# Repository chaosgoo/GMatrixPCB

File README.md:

# GMatrixPCB

该Repo为GMatrix的PCB文件，绘制软件为Autodesk Eagle。
目录下GMatrix.zip为打包的Gerber文件，直接提交到工厂即可。

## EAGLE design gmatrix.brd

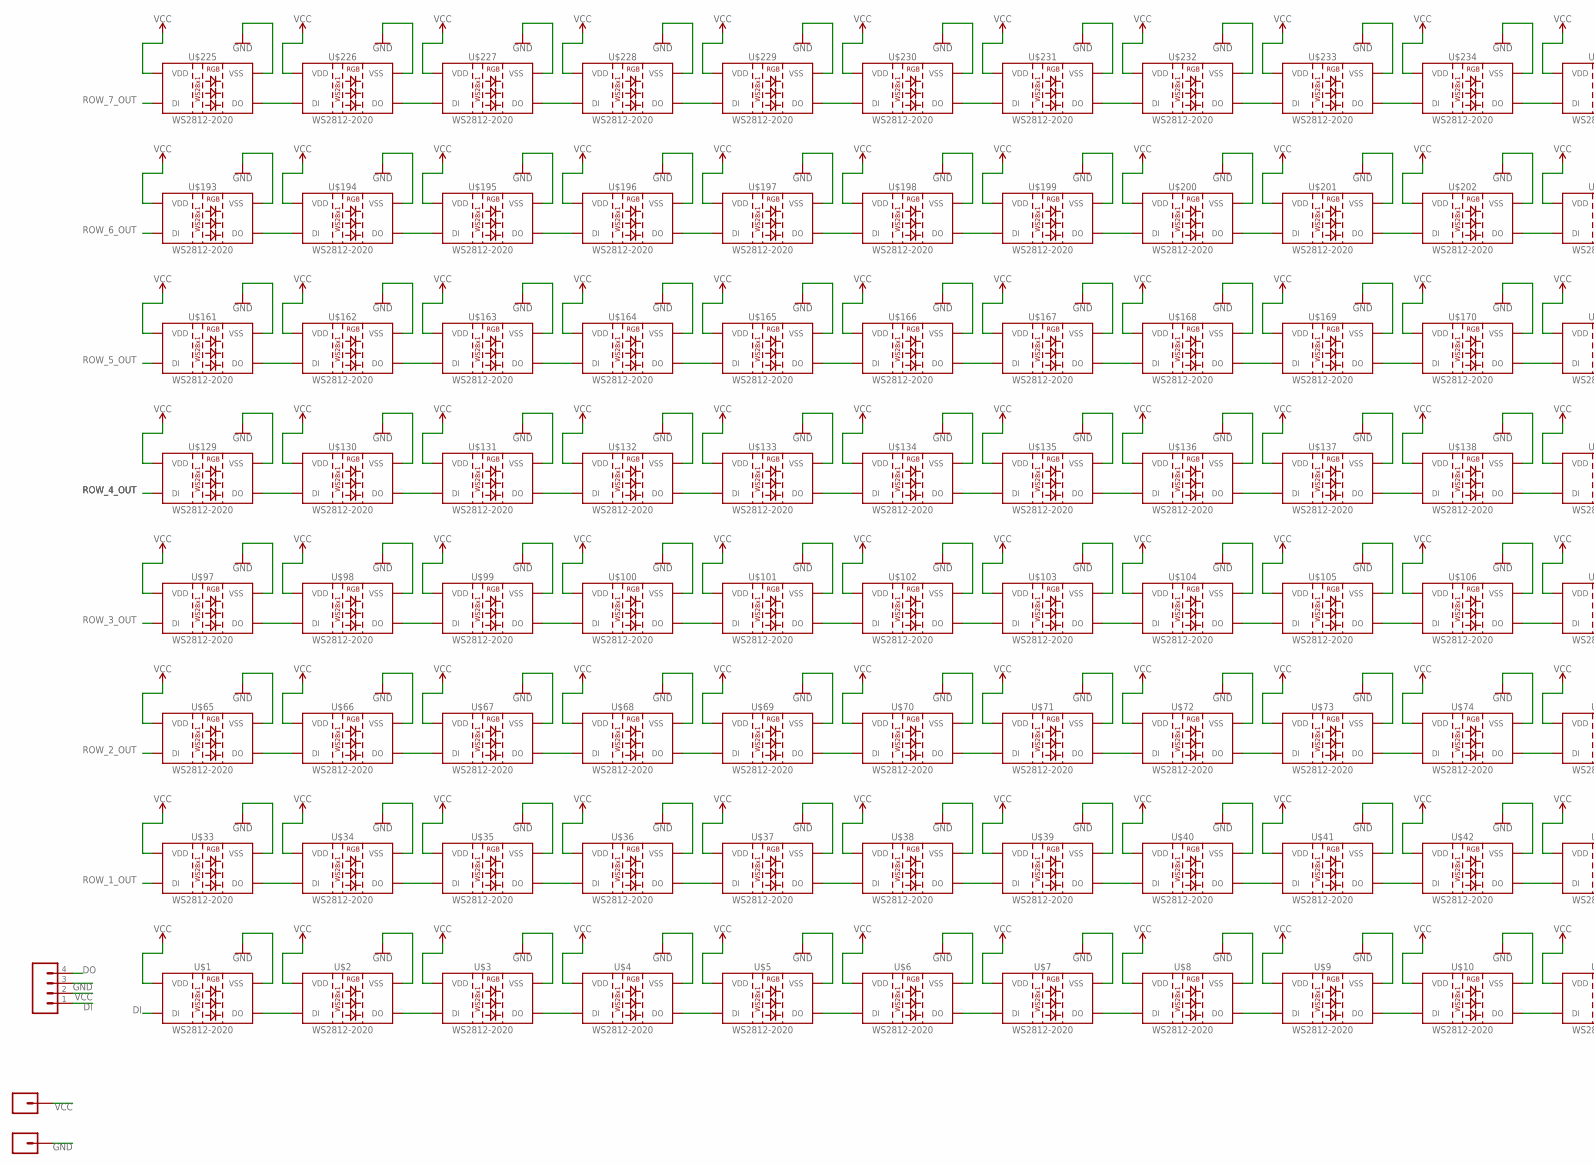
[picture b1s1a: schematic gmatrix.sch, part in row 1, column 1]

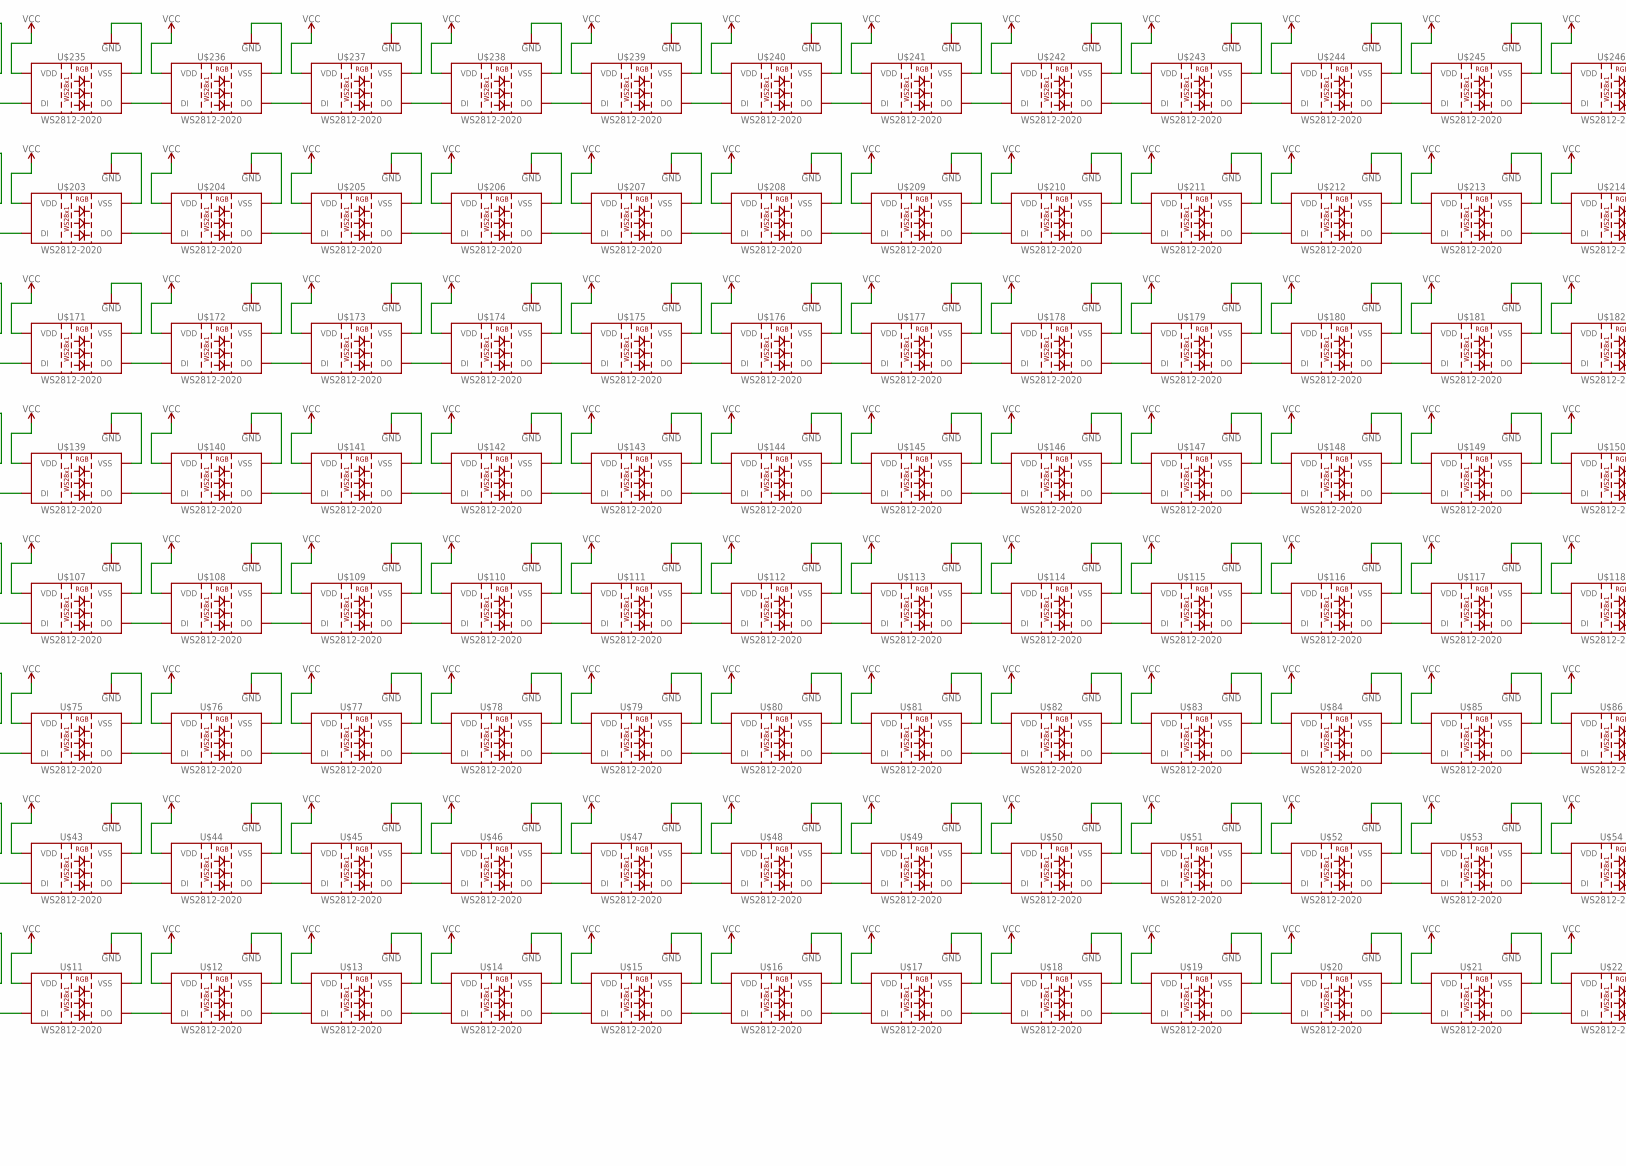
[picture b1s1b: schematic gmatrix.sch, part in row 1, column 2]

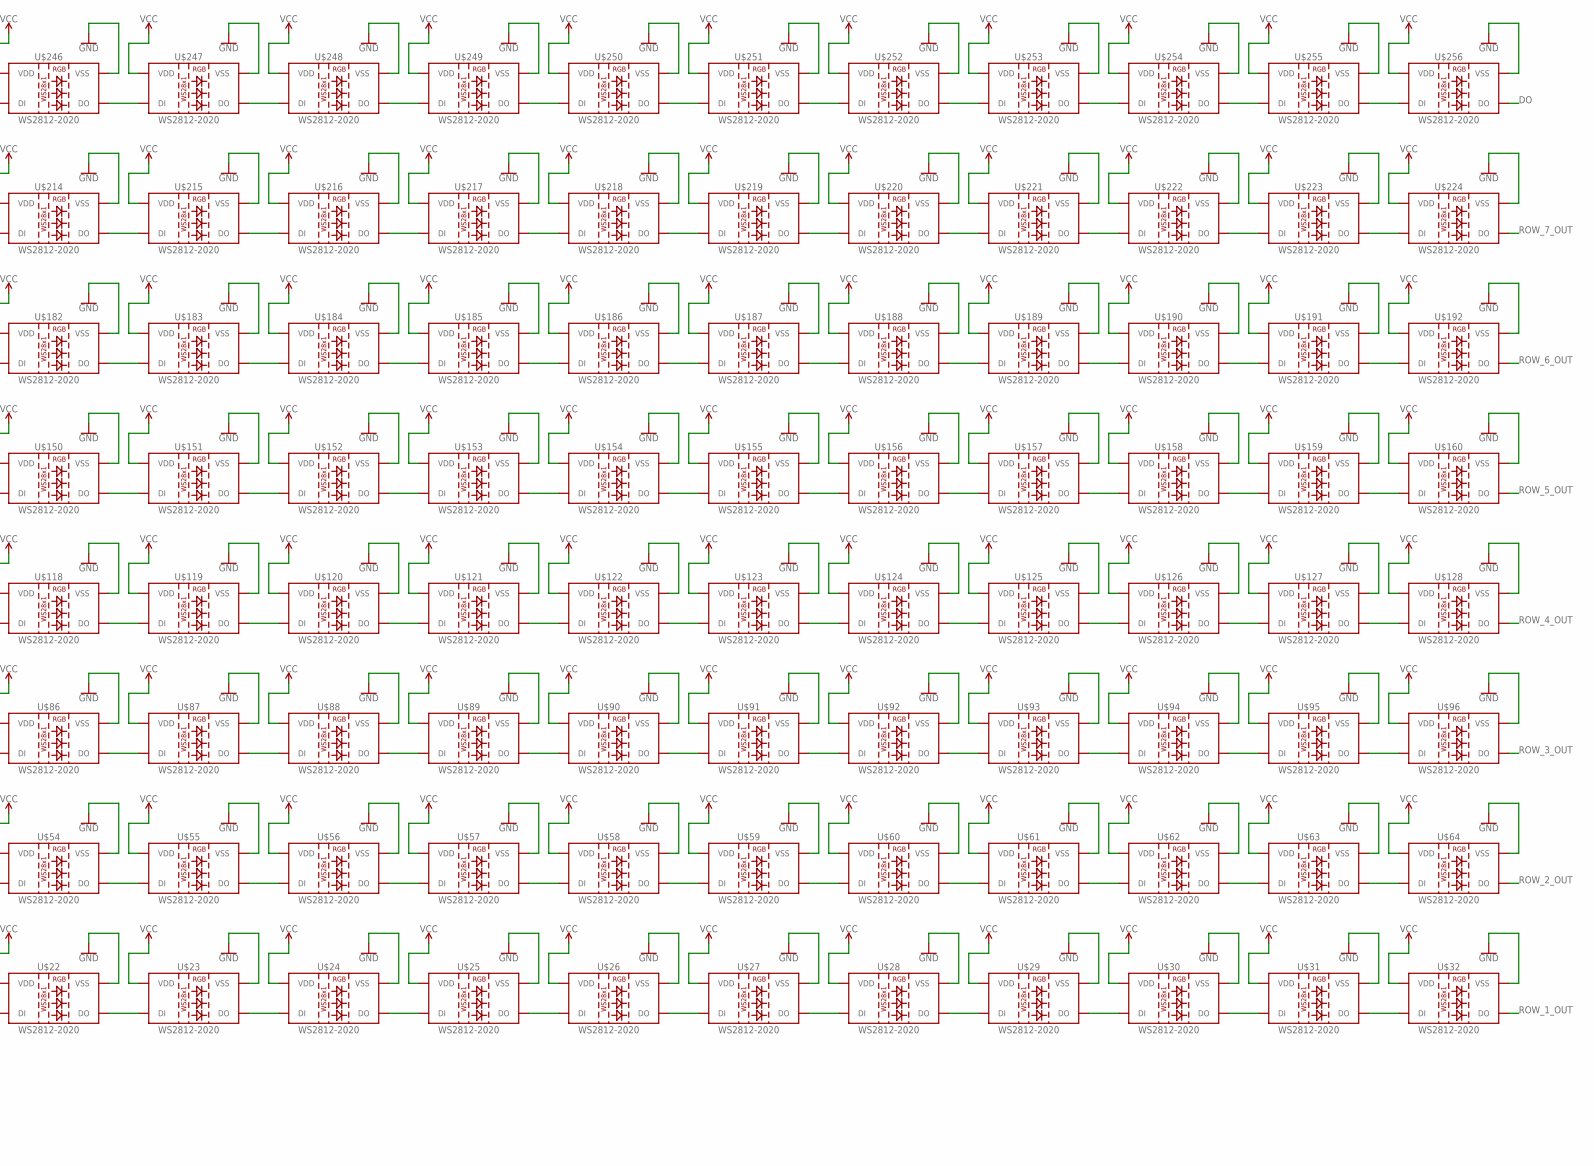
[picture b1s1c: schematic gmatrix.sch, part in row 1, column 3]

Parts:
J1: CONN_041X04_NO_SILK; 1X04_NO_SILK
J2, J3: CONN_01PTH_NO_SILK_KIT; 1X01NS_KIT
U$1, U$2, U$3, U$4, U$5, U$6, U$7, U$8, U$9, U$10, U$11, U$12, U$13, U$14, U$15, U$16, U$17, U$18, U$19, U$20, U$21, U$22, U$23, U$24, U$25, U$26, U$27, U$28, U$29, U$30, U$31, U$32, U$33, U$34, U$35, U$36, U$37, U$38, U$39, U$40, U$41, U$42, U$43, U$44, U$45, U$46, U$47, U$48, U$49, U$50, U$51, U$52, U$53, U$54, U$55, U$56, U$57, U$58, U$59, U$60, U$61, U$62, U$63, U$64, U$65, U$66, U$67, U$68, U$69, U$70, U$71, U$72, U$73, U$74, U$75, U$76, U$77, U$78, U$79, U$80, U$81, U$82, U$83, U$84, U$85, U$86, U$87, U$88, U$89, U$90, U$91, U$92, U$93, U$94, U$95, U$96, U$97, U$98, U$99, U$100, U$101, U$102, U$103, U$104, U$105, U$106, U$107, U$108, U$109, U$110, U$111, U$112, U$113, U$114, U$115, U$116, U$117, U$118, U$119, U$120, U$121, U$122, U$123, U$124, U$125, U$126, U$127, U$128, U$129, U$130, U$131, U$132, U$133, U$134, U$135, U$136, U$137, U$138, U$139, U$140, U$141, U$142, U$143, U$144, U$145, U$146, U$147, U$148, U$149, U$150, U$151, U$152, U$153, U$154, U$155, U$156, U$157, U$158, U$159, U$160, U$161, U$162, U$163, U$164, U$165, U$166, U$167, U$168, U$169, U$170, U$171, U$172, U$173, U$174, U$175, U$176, U$177, U$178, U$179, U$180, U$181, U$182, U$183, U$184, U$185, U$186, U$187, U$188, U$189, U$190, U$191, U$192, U$193, U$194, U$195, U$196, U$197, U$198, U$199, U$200, U$201, U$202, U$203, U$204, U$205, U$206, U$207, U$208, U$209, U$210, U$211, U$212, U$213, U$214, U$215, U$216, U$217, U$218, U$219, U$220, U$221, U$222, U$223, U$224, U$225, U$226, U$227, U$228, U$229, U$230, U$231, U$232, U$233, U$234, U$235, U$236, U$237, U$238, U$239, U$240, U$241, U$242, U$243, U$244, U$245, U$246, U$247, U$248, U$249, U$250, U$251, U$252, U$253, U$254, U$255, U$256: WS2812-2020

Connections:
DI: J1.1, U$1.3 (DI)
DO: J1.4, U$256.1 (DO)
GND: J1.3, J3.1, U$1.2 (VSS), U$2.2 (VSS), U$3.2 (VSS), U$4.2 (VSS), U$5.2 (VSS), U$6.2 (VSS), U$7.2 (VSS), U$8.2 (VSS), U$9.2 (VSS), U$10.2 (VSS), U$11.2 (VSS), U$12.2 (VSS), U$13.2 (VSS), U$14.2 (VSS), U$15.2 (VSS), U$16.2 (VSS), U$17.2 (VSS), U$18.2 (VSS), U$19.2 (VSS), U$20.2 (VSS), U$21.2 (VSS), U$22.2 (VSS), U$23.2 (VSS), U$24.2 (VSS), U$25.2 (VSS), U$26.2 (VSS), U$27.2 (VSS), U$28.2 (VSS), U$29.2 (VSS), U$30.2 (VSS), U$31.2 (VSS), U$32.2 (VSS), U$33.2 (VSS), U$34.2 (VSS), U$35.2 (VSS), U$36.2 (VSS), U$37.2 (VSS), U$38.2 (VSS), U$39.2 (VSS), U$40.2 (VSS), U$41.2 (VSS), U$42.2 (VSS), U$43.2 (VSS), U$44.2 (VSS), U$45.2 (VSS), U$46.2 (VSS), U$47.2 (VSS), U$48.2 (VSS), U$49.2 (VSS), U$50.2 (VSS), U$51.2 (VSS), U$52.2 (VSS), U$53.2 (VSS), U$54.2 (VSS), U$55.2 (VSS), U$56.2 (VSS), U$57.2 (VSS), U$58.2 (VSS), U$59.2 (VSS), U$60.2 (VSS), U$61.2 (VSS), U$62.2 (VSS), U$63.2 (VSS), U$64.2 (VSS), U$65.2 (VSS), U$66.2 (VSS), U$67.2 (VSS), U$68.2 (VSS), U$69.2 (VSS), U$70.2 (VSS), U$71.2 (VSS), U$72.2 (VSS), U$73.2 (VSS), U$74.2 (VSS), U$75.2 (VSS), U$76.2 (VSS), U$77.2 (VSS), U$78.2 (VSS), U$79.2 (VSS), U$80.2 (VSS), U$81.2 (VSS), U$82.2 (VSS), U$83.2 (VSS), U$84.2 (VSS), U$85.2 (VSS), U$86.2 (VSS), U$87.2 (VSS), U$88.2 (VSS), U$89.2 (VSS), U$90.2 (VSS), U$91.2 (VSS), U$92.2 (VSS), U$93.2 (VSS), U$94.2 (VSS), U$95.2 (VSS), U$96.2 (VSS), U$97.2 (VSS), U$98.2 (VSS), U$99.2 (VSS), U$100.2 (VSS), U$101.2 (VSS), U$102.2 (VSS), U$103.2 (VSS), U$104.2 (VSS), U$105.2 (VSS), U$106.2 (VSS), U$107.2 (VSS), U$108.2 (VSS), U$109.2 (VSS), U$110.2 (VSS), U$111.2 (VSS), U$112.2 (VSS), U$113.2 (VSS), U$114.2 (VSS), U$115.2 (VSS), U$116.2 (VSS), U$117.2 (VSS), U$118.2 (VSS), U$119.2 (VSS), U$120.2 (VSS), U$121.2 (VSS), U$122.2 (VSS), U$123.2 (VSS), U$124.2 (VSS), U$125.2 (VSS), U$126.2 (VSS), U$127.2 (VSS), U$128.2 (VSS), U$129.2 (VSS), U$130.2 (VSS), U$131.2 (VSS), U$132.2 (VSS), U$133.2 (VSS), U$134.2 (VSS), U$135.2 (VSS), U$136.2 (VSS), U$137.2 (VSS), U$138.2 (VSS), U$139.2 (VSS), U$140.2 (VSS), U$141.2 (VSS), U$142.2 (VSS), U$143.2 (VSS), U$144.2 (VSS), U$145.2 (VSS), U$146.2 (VSS), U$147.2 (VSS), U$148.2 (VSS), U$149.2 (VSS), U$150.2 (VSS), U$151.2 (VSS), U$152.2 (VSS), U$153.2 (VSS), U$154.2 (VSS), U$155.2 (VSS), U$156.2 (VSS), U$157.2 (VSS), U$158.2 (VSS), U$159.2 (VSS), U$160.2 (VSS), U$161.2 (VSS), U$162.2 (VSS), U$163.2 (VSS), U$164.2 (VSS), U$165.2 (VSS), U$166.2 (VSS), U$167.2 (VSS), U$168.2 (VSS), U$169.2 (VSS), U$170.2 (VSS), U$171.2 (VSS), U$172.2 (VSS), U$173.2 (VSS), U$174.2 (VSS), U$175.2 (VSS), U$176.2 (VSS), U$177.2 (VSS), U$178.2 (VSS), U$179.2 (VSS), U$180.2 (VSS), U$181.2 (VSS), U$182.2 (VSS), U$183.2 (VSS), U$184.2 (VSS), U$185.2 (VSS), U$186.2 (VSS), U$187.2 (VSS), U$188.2 (VSS), U$189.2 (VSS), U$190.2 (VSS), U$191.2 (VSS), U$192.2 (VSS), U$193.2 (VSS), U$194.2 (VSS), U$195.2 (VSS), U$196.2 (VSS), U$197.2 (VSS), U$198.2 (VSS), U$199.2 (VSS), U$200.2 (VSS), U$201.2 (VSS), U$202.2 (VSS), U$203.2 (VSS), U$204.2 (VSS), U$205.2 (VSS), U$206.2 (VSS), U$207.2 (VSS), U$208.2 (VSS), U$209.2 (VSS), U$210.2 (VSS), U$211.2 (VSS), U$212.2 (VSS), U$213.2 (VSS), U$214.2 (VSS), U$215.2 (VSS), U$216.2 (VSS), U$217.2 (VSS), U$218.2 (VSS), U$219.2 (VSS), U$220.2 (VSS), U$221.2 (VSS), U$222.2 (VSS), U$223.2 (VSS), U$224.2 (VSS), U$225.2 (VSS), U$226.2 (VSS), U$227.2 (VSS), U$228.2 (VSS), U$229.2 (VSS), U$230.2 (VSS), U$231.2 (VSS), U$232.2 (VSS), U$233.2 (VSS), U$234.2 (VSS), U$235.2 (VSS), U$236.2 (VSS), U$237.2 (VSS), U$238.2 (VSS), U$239.2 (VSS), U$240.2 (VSS), U$241.2 (VSS), U$242.2 (VSS), U$243.2 (VSS), U$244.2 (VSS), U$245.2 (VSS), U$246.2 (VSS), U$247.2 (VSS), U$248.2 (VSS), U$249.2 (VSS), U$250.2 (VSS), U$251.2 (VSS), U$252.2 (VSS), U$253.2 (VSS), U$254.2 (VSS), U$255.2 (VSS), U$256.2 (VSS)
unnamed: U$1.1 (DO), U$2.3 (DI)
unnamed: U$2.1 (DO), U$3.3 (DI)
unnamed: U$3.1 (DO), U$4.3 (DI)
unnamed: U$4.1 (DO), U$5.3 (DI)
unnamed: U$5.1 (DO), U$6.3 (DI)
unnamed: U$6.1 (DO), U$7.3 (DI)
unnamed: U$7.1 (DO), U$8.3 (DI)
unnamed: U$8.1 (DO), U$9.3 (DI)
unnamed: U$9.1 (DO), U$10.3 (DI)
unnamed: U$10.1 (DO), U$11.3 (DI)
unnamed: U$11.1 (DO), U$12.3 (DI)
unnamed: U$12.1 (DO), U$13.3 (DI)
unnamed: U$13.1 (DO), U$14.3 (DI)
unnamed: U$14.1 (DO), U$15.3 (DI)
unnamed: U$15.1 (DO), U$16.3 (DI)
unnamed: U$16.1 (DO), U$17.3 (DI)
unnamed: U$17.1 (DO), U$18.3 (DI)
unnamed: U$18.1 (DO), U$19.3 (DI)
unnamed: U$19.1 (DO), U$20.3 (DI)
unnamed: U$20.1 (DO), U$21.3 (DI)
unnamed: U$21.1 (DO), U$22.3 (DI)
unnamed: U$22.1 (DO), U$23.3 (DI)
unnamed: U$23.1 (DO), U$24.3 (DI)
unnamed: U$24.1 (DO), U$25.3 (DI)
unnamed: U$25.1 (DO), U$26.3 (DI)
unnamed: U$26.1 (DO), U$27.3 (DI)
unnamed: U$27.1 (DO), U$28.3 (DI)
unnamed: U$28.1 (DO), U$29.3 (DI)
unnamed: U$29.1 (DO), U$30.3 (DI)
unnamed: U$30.1 (DO), U$31.3 (DI)
unnamed: U$31.1 (DO), U$32.3 (DI)
unnamed: U$33.1 (DO), U$34.3 (DI)
unnamed: U$34.1 (DO), U$35.3 (DI)
unnamed: U$35.1 (DO), U$36.3 (DI)
unnamed: U$36.1 (DO), U$37.3 (DI)
unnamed: U$37.1 (DO), U$38.3 (DI)
unnamed: U$38.1 (DO), U$39.3 (DI)
unnamed: U$39.1 (DO), U$40.3 (DI)
unnamed: U$40.1 (DO), U$41.3 (DI)
unnamed: U$41.1 (DO), U$42.3 (DI)
unnamed: U$42.1 (DO), U$43.3 (DI)
unnamed: U$43.1 (DO), U$44.3 (DI)
unnamed: U$44.1 (DO), U$45.3 (DI)
unnamed: U$45.1 (DO), U$46.3 (DI)
unnamed: U$46.1 (DO), U$47.3 (DI)
unnamed: U$47.1 (DO), U$48.3 (DI)
unnamed: U$48.1 (DO), U$49.3 (DI)
unnamed: U$49.1 (DO), U$50.3 (DI)
unnamed: U$50.1 (DO), U$51.3 (DI)
unnamed: U$51.1 (DO), U$52.3 (DI)
unnamed: U$52.1 (DO), U$53.3 (DI)
unnamed: U$53.1 (DO), U$54.3 (DI)
unnamed: U$54.1 (DO), U$55.3 (DI)
unnamed: U$55.1 (DO), U$56.3 (DI)
unnamed: U$56.1 (DO), U$57.3 (DI)
unnamed: U$57.1 (DO), U$58.3 (DI)
unnamed: U$58.1 (DO), U$59.3 (DI)
unnamed: U$59.1 (DO), U$60.3 (DI)
unnamed: U$60.1 (DO), U$61.3 (DI)
unnamed: U$61.1 (DO), U$62.3 (DI)
unnamed: U$62.1 (DO), U$63.3 (DI)
unnamed: U$63.1 (DO), U$64.3 (DI)
unnamed: U$65.1 (DO), U$66.3 (DI)
unnamed: U$66.1 (DO), U$67.3 (DI)
unnamed: U$67.1 (DO), U$68.3 (DI)
unnamed: U$68.1 (DO), U$69.3 (DI)
unnamed: U$69.1 (DO), U$70.3 (DI)
unnamed: U$70.1 (DO), U$71.3 (DI)
unnamed: U$71.1 (DO), U$72.3 (DI)
unnamed: U$72.1 (DO), U$73.3 (DI)
unnamed: U$73.1 (DO), U$74.3 (DI)
unnamed: U$74.1 (DO), U$75.3 (DI)
unnamed: U$75.1 (DO), U$76.3 (DI)
unnamed: U$76.1 (DO), U$77.3 (DI)
unnamed: U$77.1 (DO), U$78.3 (DI)
unnamed: U$78.1 (DO), U$79.3 (DI)
unnamed: U$79.1 (DO), U$80.3 (DI)
unnamed: U$80.1 (DO), U$81.3 (DI)
unnamed: U$81.1 (DO), U$82.3 (DI)
unnamed: U$82.1 (DO), U$83.3 (DI)
unnamed: U$83.1 (DO), U$84.3 (DI)
unnamed: U$84.1 (DO), U$85.3 (DI)
unnamed: U$85.1 (DO), U$86.3 (DI)
unnamed: U$86.1 (DO), U$87.3 (DI)
unnamed: U$87.1 (DO), U$88.3 (DI)
unnamed: U$88.1 (DO), U$89.3 (DI)
unnamed: U$89.1 (DO), U$90.3 (DI)
unnamed: U$90.1 (DO), U$91.3 (DI)
unnamed: U$91.1 (DO), U$92.3 (DI)
unnamed: U$92.1 (DO), U$93.3 (DI)
unnamed: U$93.1 (DO), U$94.3 (DI)
unnamed: U$94.1 (DO), U$95.3 (DI)
unnamed: U$95.1 (DO), U$96.3 (DI)
unnamed: U$97.1 (DO), U$98.3 (DI)
unnamed: U$98.1 (DO), U$99.3 (DI)
unnamed: U$99.1 (DO), U$100.3 (DI)
unnamed: U$100.1 (DO), U$101.3 (DI)
unnamed: U$101.1 (DO), U$102.3 (DI)
unnamed: U$102.1 (DO), U$103.3 (DI)
unnamed: U$103.1 (DO), U$104.3 (DI)
unnamed: U$104.1 (DO), U$105.3 (DI)
unnamed: U$105.1 (DO), U$106.3 (DI)
unnamed: U$106.1 (DO), U$107.3 (DI)
unnamed: U$107.1 (DO), U$108.3 (DI)
unnamed: U$108.1 (DO), U$109.3 (DI)
unnamed: U$109.1 (DO), U$110.3 (DI)
unnamed: U$110.1 (DO), U$111.3 (DI)
unnamed: U$111.1 (DO), U$112.3 (DI)
unnamed: U$112.1 (DO), U$113.3 (DI)
unnamed: U$113.1 (DO), U$114.3 (DI)
unnamed: U$114.1 (DO), U$115.3 (DI)
unnamed: U$115.1 (DO), U$116.3 (DI)
unnamed: U$116.1 (DO), U$117.3 (DI)
unnamed: U$117.1 (DO), U$118.3 (DI)
unnamed: U$118.1 (DO), U$119.3 (DI)
unnamed: U$119.1 (DO), U$120.3 (DI)
unnamed: U$120.1 (DO), U$121.3 (DI)
unnamed: U$121.1 (DO), U$122.3 (DI)
unnamed: U$122.1 (DO), U$123.3 (DI)
unnamed: U$123.1 (DO), U$124.3 (DI)
unnamed: U$124.1 (DO), U$125.3 (DI)
unnamed: U$125.1 (DO), U$126.3 (DI)
unnamed: U$126.1 (DO), U$127.3 (DI)
unnamed: U$127.1 (DO), U$128.3 (DI)
unnamed: U$129.1 (DO), U$130.3 (DI)
unnamed: U$130.1 (DO), U$131.3 (DI)
unnamed: U$131.1 (DO), U$132.3 (DI)
unnamed: U$132.1 (DO), U$133.3 (DI)
unnamed: U$133.1 (DO), U$134.3 (DI)
unnamed: U$134.1 (DO), U$135.3 (DI)
unnamed: U$135.1 (DO), U$136.3 (DI)
unnamed: U$136.1 (DO), U$137.3 (DI)
unnamed: U$137.1 (DO), U$138.3 (DI)
unnamed: U$138.1 (DO), U$139.3 (DI)
unnamed: U$139.1 (DO), U$140.3 (DI)
unnamed: U$140.1 (DO), U$141.3 (DI)
unnamed: U$141.1 (DO), U$142.3 (DI)
unnamed: U$142.1 (DO), U$143.3 (DI)
unnamed: U$143.1 (DO), U$144.3 (DI)
unnamed: U$144.1 (DO), U$145.3 (DI)
unnamed: U$145.1 (DO), U$146.3 (DI)
unnamed: U$146.1 (DO), U$147.3 (DI)
unnamed: U$147.1 (DO), U$148.3 (DI)
unnamed: U$148.1 (DO), U$149.3 (DI)
unnamed: U$149.1 (DO), U$150.3 (DI)
unnamed: U$150.1 (DO), U$151.3 (DI)
unnamed: U$151.1 (DO), U$152.3 (DI)
unnamed: U$152.1 (DO), U$153.3 (DI)
unnamed: U$153.1 (DO), U$154.3 (DI)
unnamed: U$154.1 (DO), U$155.3 (DI)
unnamed: U$155.1 (DO), U$156.3 (DI)
unnamed: U$156.1 (DO), U$157.3 (DI)
unnamed: U$157.1 (DO), U$158.3 (DI)
unnamed: U$158.1 (DO), U$159.3 (DI)
unnamed: U$159.1 (DO), U$160.3 (DI)
unnamed: U$161.1 (DO), U$162.3 (DI)
unnamed: U$162.1 (DO), U$163.3 (DI)
unnamed: U$163.1 (DO), U$164.3 (DI)
unnamed: U$164.1 (DO), U$165.3 (DI)
unnamed: U$165.1 (DO), U$166.3 (DI)
unnamed: U$166.1 (DO), U$167.3 (DI)
unnamed: U$167.1 (DO), U$168.3 (DI)
unnamed: U$168.1 (DO), U$169.3 (DI)
unnamed: U$169.1 (DO), U$170.3 (DI)
unnamed: U$170.1 (DO), U$171.3 (DI)
unnamed: U$171.1 (DO), U$172.3 (DI)
unnamed: U$172.1 (DO), U$173.3 (DI)
unnamed: U$173.1 (DO), U$174.3 (DI)
unnamed: U$174.1 (DO), U$175.3 (DI)
unnamed: U$175.1 (DO), U$176.3 (DI)
unnamed: U$176.1 (DO), U$177.3 (DI)
unnamed: U$177.1 (DO), U$178.3 (DI)
unnamed: U$178.1 (DO), U$179.3 (DI)
unnamed: U$179.1 (DO), U$180.3 (DI)
unnamed: U$180.1 (DO), U$181.3 (DI)
unnamed: U$181.1 (DO), U$182.3 (DI)
unnamed: U$182.1 (DO), U$183.3 (DI)
unnamed: U$183.1 (DO), U$184.3 (DI)
unnamed: U$184.1 (DO), U$185.3 (DI)
unnamed: U$185.1 (DO), U$186.3 (DI)
unnamed: U$186.1 (DO), U$187.3 (DI)
unnamed: U$187.1 (DO), U$188.3 (DI)
unnamed: U$188.1 (DO), U$189.3 (DI)
unnamed: U$189.1 (DO), U$190.3 (DI)
unnamed: U$190.1 (DO), U$191.3 (DI)
unnamed: U$191.1 (DO), U$192.3 (DI)
unnamed: U$193.1 (DO), U$194.3 (DI)
unnamed: U$194.1 (DO), U$195.3 (DI)
unnamed: U$195.1 (DO), U$196.3 (DI)
unnamed: U$196.1 (DO), U$197.3 (DI)
unnamed: U$197.1 (DO), U$198.3 (DI)
unnamed: U$198.1 (DO), U$199.3 (DI)
unnamed: U$199.1 (DO), U$200.3 (DI)
unnamed: U$200.1 (DO), U$201.3 (DI)
unnamed: U$201.1 (DO), U$202.3 (DI)
unnamed: U$202.1 (DO), U$203.3 (DI)
unnamed: U$203.1 (DO), U$204.3 (DI)
unnamed: U$204.1 (DO), U$205.3 (DI)
unnamed: U$205.1 (DO), U$206.3 (DI)
unnamed: U$206.1 (DO), U$207.3 (DI)
unnamed: U$207.1 (DO), U$208.3 (DI)
unnamed: U$208.1 (DO), U$209.3 (DI)
unnamed: U$209.1 (DO), U$210.3 (DI)
unnamed: U$210.1 (DO), U$211.3 (DI)
unnamed: U$211.1 (DO), U$212.3 (DI)
unnamed: U$212.1 (DO), U$213.3 (DI)
unnamed: U$213.1 (DO), U$214.3 (DI)
unnamed: U$214.1 (DO), U$215.3 (DI)
unnamed: U$215.1 (DO), U$216.3 (DI)
unnamed: U$216.1 (DO), U$217.3 (DI)
unnamed: U$217.1 (DO), U$218.3 (DI)
unnamed: U$218.1 (DO), U$219.3 (DI)
unnamed: U$219.1 (DO), U$220.3 (DI)
unnamed: U$220.1 (DO), U$221.3 (DI)
unnamed: U$221.1 (DO), U$222.3 (DI)
unnamed: U$222.1 (DO), U$223.3 (DI)
unnamed: U$223.1 (DO), U$224.3 (DI)
unnamed: U$225.1 (DO), U$226.3 (DI)
unnamed: U$226.1 (DO), U$227.3 (DI)
unnamed: U$227.1 (DO), U$228.3 (DI)
unnamed: U$228.1 (DO), U$229.3 (DI)
unnamed: U$229.1 (DO), U$230.3 (DI)
unnamed: U$230.1 (DO), U$231.3 (DI)
unnamed: U$231.1 (DO), U$232.3 (DI)
unnamed: U$232.1 (DO), U$233.3 (DI)
unnamed: U$233.1 (DO), U$234.3 (DI)
unnamed: U$234.1 (DO), U$235.3 (DI)
unnamed: U$235.1 (DO), U$236.3 (DI)
unnamed: U$236.1 (DO), U$237.3 (DI)
unnamed: U$237.1 (DO), U$238.3 (DI)
unnamed: U$238.1 (DO), U$239.3 (DI)
unnamed: U$239.1 (DO), U$240.3 (DI)
unnamed: U$240.1 (DO), U$241.3 (DI)
unnamed: U$241.1 (DO), U$242.3 (DI)
unnamed: U$242.1 (DO), U$243.3 (DI)
unnamed: U$243.1 (DO), U$244.3 (DI)
unnamed: U$244.1 (DO), U$245.3 (DI)
unnamed: U$245.1 (DO), U$246.3 (DI)
unnamed: U$246.1 (DO), U$247.3 (DI)
unnamed: U$247.1 (DO), U$248.3 (DI)
unnamed: U$248.1 (DO), U$249.3 (DI)
unnamed: U$249.1 (DO), U$250.3 (DI)
unnamed: U$250.1 (DO), U$251.3 (DI)
unnamed: U$251.1 (DO), U$252.3 (DI)
unnamed: U$252.1 (DO), U$253.3 (DI)
unnamed: U$253.1 (DO), U$254.3 (DI)
unnamed: U$254.1 (DO), U$255.3 (DI)
unnamed: U$255.1 (DO), U$256.3 (DI)
ROW_1_OUT: U$32.1 (DO), U$33.3 (DI)
ROW_2_OUT: U$64.1 (DO), U$65.3 (DI)
ROW_3_OUT: U$96.1 (DO), U$97.3 (DI)
ROW_4_OUT: U$128.1 (DO), U$129.3 (DI)
ROW_5_OUT: U$160.1 (DO), U$161.3 (DI)
ROW_6_OUT: U$192.1 (DO), U$193.3 (DI)
ROW_7_OUT: U$224.1 (DO), U$225.3 (DI)
VCC: J1.2, J2.1, U$1.4 (VDD), U$2.4 (VDD), U$3.4 (VDD), U$4.4 (VDD), U$5.4 (VDD), U$6.4 (VDD), U$7.4 (VDD), U$8.4 (VDD), U$9.4 (VDD), U$10.4 (VDD), U$11.4 (VDD), U$12.4 (VDD), U$13.4 (VDD), U$14.4 (VDD), U$15.4 (VDD), U$16.4 (VDD), U$17.4 (VDD), U$18.4 (VDD), U$19.4 (VDD), U$20.4 (VDD), U$21.4 (VDD), U$22.4 (VDD), U$23.4 (VDD), U$24.4 (VDD), U$25.4 (VDD), U$26.4 (VDD), U$27.4 (VDD), U$28.4 (VDD), U$29.4 (VDD), U$30.4 (VDD), U$31.4 (VDD), U$32.4 (VDD), U$33.4 (VDD), U$34.4 (VDD), U$35.4 (VDD), U$36.4 (VDD), U$37.4 (VDD), U$38.4 (VDD), U$39.4 (VDD), U$40.4 (VDD), U$41.4 (VDD), U$42.4 (VDD), U$43.4 (VDD), U$44.4 (VDD), U$45.4 (VDD), U$46.4 (VDD), U$47.4 (VDD), U$48.4 (VDD), U$49.4 (VDD), U$50.4 (VDD), U$51.4 (VDD), U$52.4 (VDD), U$53.4 (VDD), U$54.4 (VDD), U$55.4 (VDD), U$56.4 (VDD), U$57.4 (VDD), U$58.4 (VDD), U$59.4 (VDD), U$60.4 (VDD), U$61.4 (VDD), U$62.4 (VDD), U$63.4 (VDD), U$64.4 (VDD), U$65.4 (VDD), U$66.4 (VDD), U$67.4 (VDD), U$68.4 (VDD), U$69.4 (VDD), U$70.4 (VDD), U$71.4 (VDD), U$72.4 (VDD), U$73.4 (VDD), U$74.4 (VDD), U$75.4 (VDD), U$76.4 (VDD), U$77.4 (VDD), U$78.4 (VDD), U$79.4 (VDD), U$80.4 (VDD), U$81.4 (VDD), U$82.4 (VDD), U$83.4 (VDD), U$84.4 (VDD), U$85.4 (VDD), U$86.4 (VDD), U$87.4 (VDD), U$88.4 (VDD), U$89.4 (VDD), U$90.4 (VDD), U$91.4 (VDD), U$92.4 (VDD), U$93.4 (VDD), U$94.4 (VDD), U$95.4 (VDD), U$96.4 (VDD), U$97.4 (VDD), U$98.4 (VDD), U$99.4 (VDD), U$100.4 (VDD), U$101.4 (VDD), U$102.4 (VDD), U$103.4 (VDD), U$104.4 (VDD), U$105.4 (VDD), U$106.4 (VDD), U$107.4 (VDD), U$108.4 (VDD), U$109.4 (VDD), U$110.4 (VDD), U$111.4 (VDD), U$112.4 (VDD), U$113.4 (VDD), U$114.4 (VDD), U$115.4 (VDD), U$116.4 (VDD), U$117.4 (VDD), U$118.4 (VDD), U$119.4 (VDD), U$120.4 (VDD), U$121.4 (VDD), U$122.4 (VDD), U$123.4 (VDD), U$124.4 (VDD), U$125.4 (VDD), U$126.4 (VDD), U$127.4 (VDD), U$128.4 (VDD), U$129.4 (VDD), U$130.4 (VDD), U$131.4 (VDD), U$132.4 (VDD), U$133.4 (VDD), U$134.4 (VDD), U$135.4 (VDD), U$136.4 (VDD), U$137.4 (VDD), U$138.4 (VDD), U$139.4 (VDD), U$140.4 (VDD), U$141.4 (VDD), U$142.4 (VDD), U$143.4 (VDD), U$144.4 (VDD), U$145.4 (VDD), U$146.4 (VDD), U$147.4 (VDD), U$148.4 (VDD), U$149.4 (VDD), U$150.4 (VDD), U$151.4 (VDD), U$152.4 (VDD), U$153.4 (VDD), U$154.4 (VDD), U$155.4 (VDD), U$156.4 (VDD), U$157.4 (VDD), U$158.4 (VDD), U$159.4 (VDD), U$160.4 (VDD), U$161.4 (VDD), U$162.4 (VDD), U$163.4 (VDD), U$164.4 (VDD), U$165.4 (VDD), U$166.4 (VDD), U$167.4 (VDD), U$168.4 (VDD), U$169.4 (VDD), U$170.4 (VDD), U$171.4 (VDD), U$172.4 (VDD), U$173.4 (VDD), U$174.4 (VDD), U$175.4 (VDD), U$176.4 (VDD), U$177.4 (VDD), U$178.4 (VDD), U$179.4 (VDD), U$180.4 (VDD), U$181.4 (VDD), U$182.4 (VDD), U$183.4 (VDD), U$184.4 (VDD), U$185.4 (VDD), U$186.4 (VDD), U$187.4 (VDD), U$188.4 (VDD), U$189.4 (VDD), U$190.4 (VDD), U$191.4 (VDD), U$192.4 (VDD), U$193.4 (VDD), U$194.4 (VDD), U$195.4 (VDD), U$196.4 (VDD), U$197.4 (VDD), U$198.4 (VDD), U$199.4 (VDD), U$200.4 (VDD), U$201.4 (VDD), U$202.4 (VDD), U$203.4 (VDD), U$204.4 (VDD), U$205.4 (VDD), U$206.4 (VDD), U$207.4 (VDD), U$208.4 (VDD), U$209.4 (VDD), U$210.4 (VDD), U$211.4 (VDD), U$212.4 (VDD), U$213.4 (VDD), U$214.4 (VDD), U$215.4 (VDD), U$216.4 (VDD), U$217.4 (VDD), U$218.4 (VDD), U$219.4 (VDD), U$220.4 (VDD), U$221.4 (VDD), U$222.4 (VDD), U$223.4 (VDD), U$224.4 (VDD), U$225.4 (VDD), U$226.4 (VDD), U$227.4 (VDD), U$228.4 (VDD), U$229.4 (VDD), U$230.4 (VDD), U$231.4 (VDD), U$232.4 (VDD), U$233.4 (VDD), U$234.4 (VDD), U$235.4 (VDD), U$236.4 (VDD), U$237.4 (VDD), U$238.4 (VDD), U$239.4 (VDD), U$240.4 (VDD), U$241.4 (VDD), U$242.4 (VDD), U$243.4 (VDD), U$244.4 (VDD), U$245.4 (VDD), U$246.4 (VDD), U$247.4 (VDD), U$248.4 (VDD), U$249.4 (VDD), U$250.4 (VDD), U$251.4 (VDD), U$252.4 (VDD), U$253.4 (VDD), U$254.4 (VDD), U$255.4 (VDD), U$256.4 (VDD)

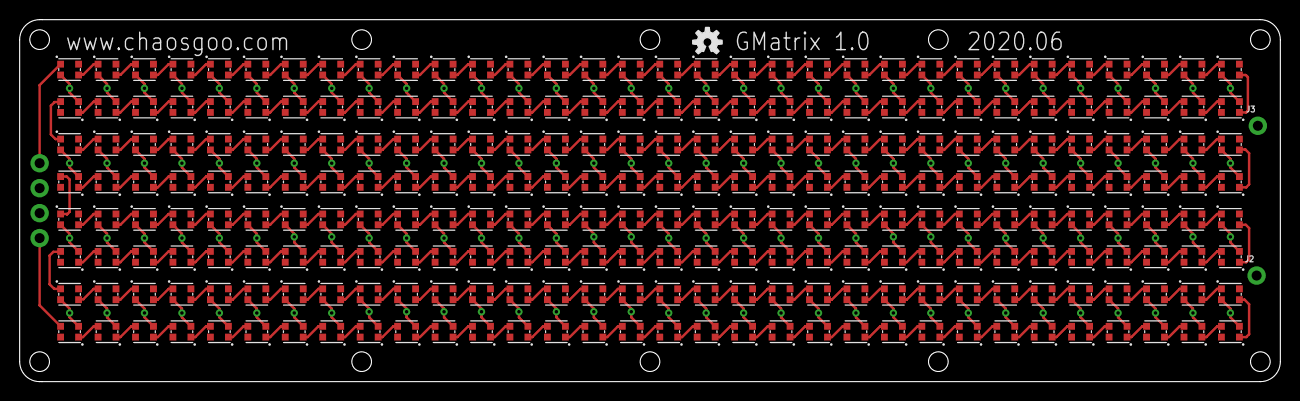
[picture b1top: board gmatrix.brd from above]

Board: 2 copper layers, 128.3 x 36.8 mm, 260 parts (1 on the bottom side), 259 nets.

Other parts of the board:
U$257: OSHW-LOGO-S

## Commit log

2020-07-20 add README.md

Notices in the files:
parts and their libraries:
SparkFun-LED: Licensing: Creative Commons ShareAlike 4.0 International - https://creativecommons.org/licenses/by-sa/4.0
